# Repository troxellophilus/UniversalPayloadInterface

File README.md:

# UniversalPayloadInterface
Universal UAV Payload Interface Senior Project

Open Source Code & Hardware

Cal Poly SLO

* Nolan Reker
* Drew Troxell
* David Troy

More documentation coming soon!

### Getting Started

#### Requirements
* UAV utilizing the Mavlink protocol
* Onboard proxy device for running MAVProxy
* Atmega328p on payload interface board (see pcb directory for hardware details)

#### Loading the source
* Compile and upload the payload_atmega328p ino project to the atmega328p payload interface board using your favorite AVR compiler/loader.
* Connect the interface board to the onboard device via UART.
* Run MAVProxy on the onboard device w/ the master device set to the autopilot and the output device set to the UART connection to the interface board.
* The onboard LED will light up after successfully receiving 10 heartbeat packets from the autopilot.

#### Modifying the source
This code is meant to provide a simple example and framework for communicating between a payload and an autopilot via Mavlink. Reference the mavlink library for functions to decode or send more messages via mavlink.

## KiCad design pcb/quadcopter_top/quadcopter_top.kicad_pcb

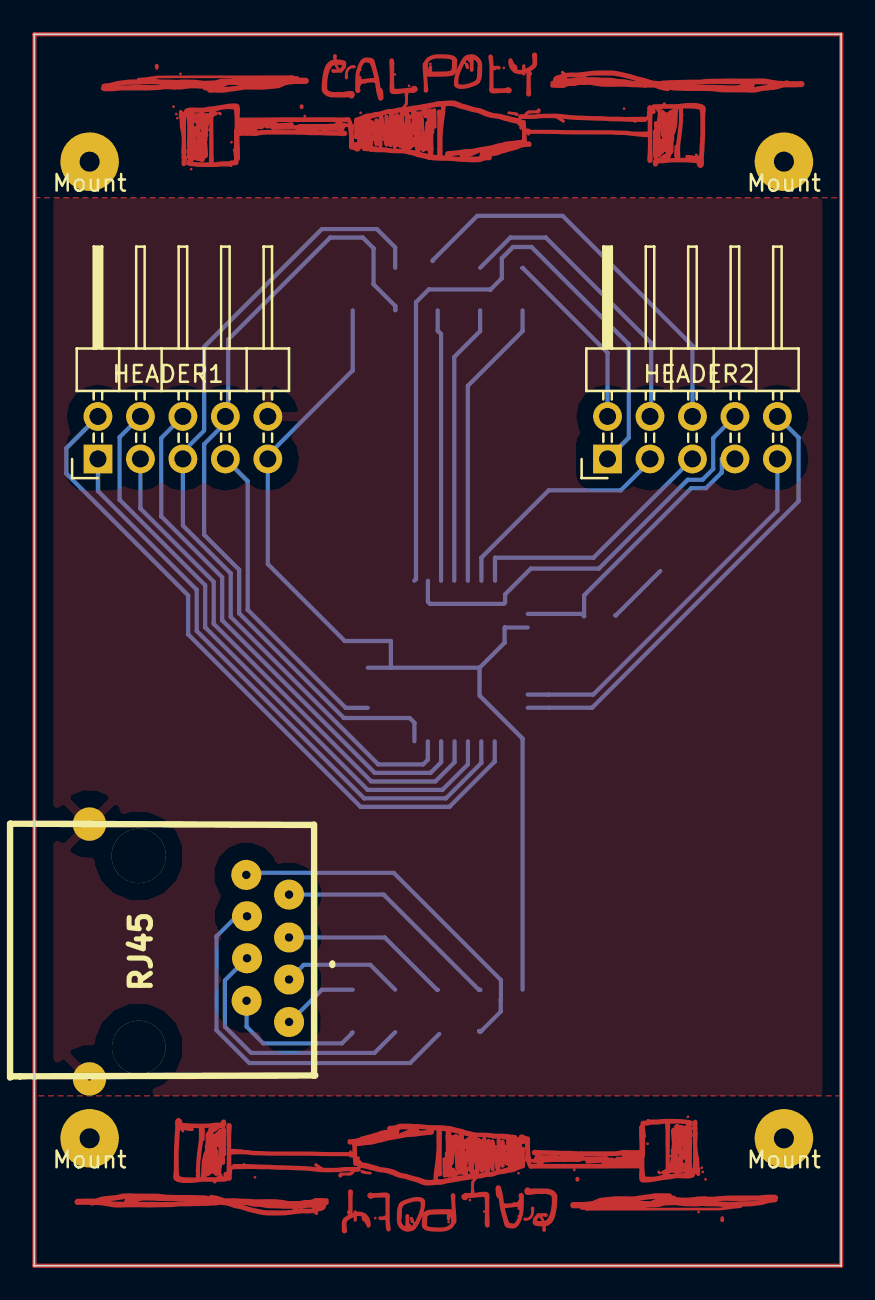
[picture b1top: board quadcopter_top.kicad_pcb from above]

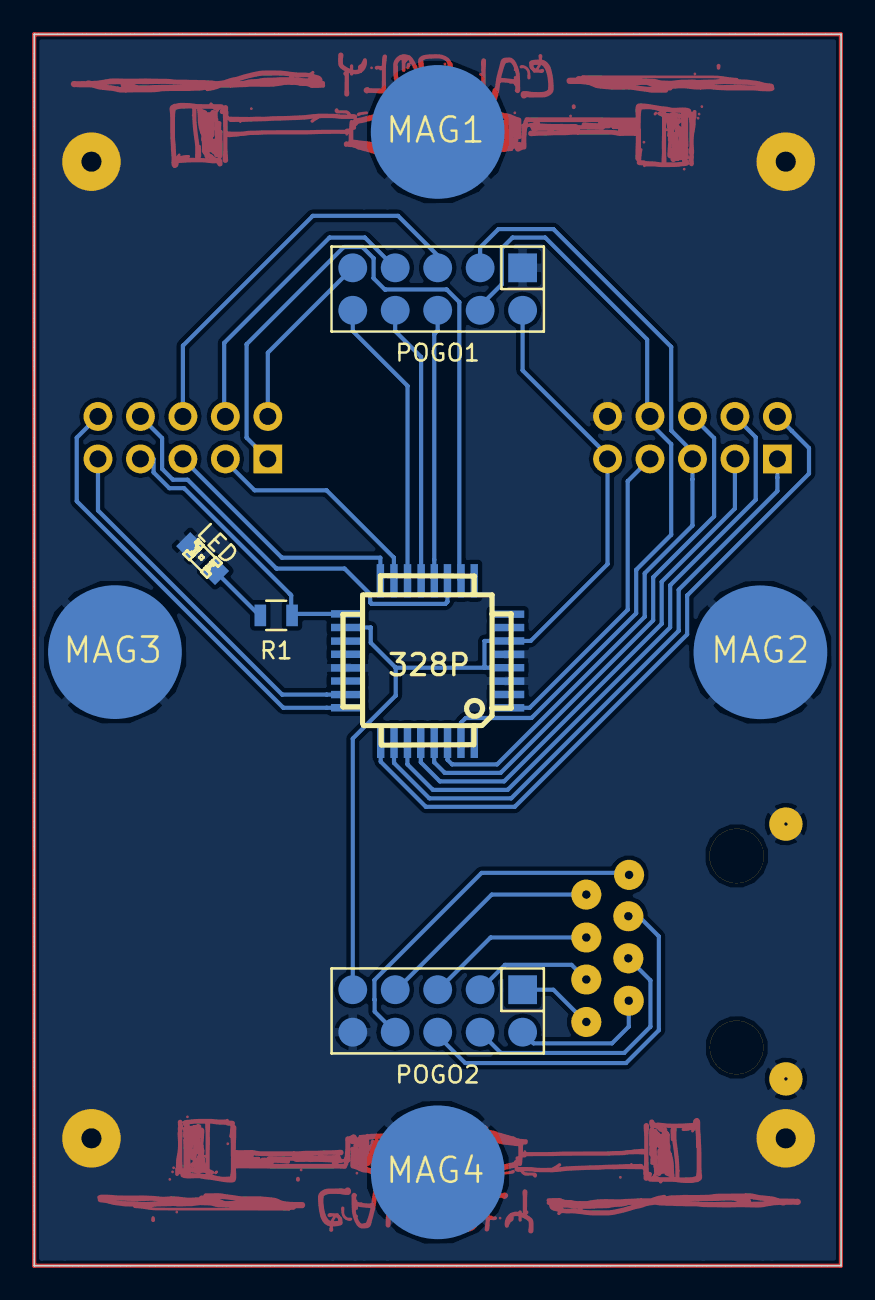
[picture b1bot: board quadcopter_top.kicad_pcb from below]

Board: 2 copper layers, 48.3 x 73.7 mm, 16 parts (9 on the bottom side), 32 nets.

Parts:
328P: ATMEGA328P-A; TQFP32_08
HEADER1, HEADER2: CONN_02X05; Pin_Header_Angled_2x05
J1: RJ45
LED: LED; LED-0805
MAG1, MAG2, MAG3, MAG4: CONN_01X01; 8mmMagnet
Mount: Mount; SolderWirePad_single_1-2mmDrill
Mount#2, Mount#3, Mount#4: Mount; SolderWirePad_single_1-2mmDrill
POGO1, POGO2: CONN_02X05; Pin_Header_Straight_2x05_SMD
R1: R; R_0805

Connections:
+5V: 328P.4, 328P.6, 328P.18, HEADER1.9, POGO1.2, POGO2.9
GND: 328P.3, 328P.5, 328P.21, HEADER1.10, J1.9, LED.1, MAG1.1, MAG2.1, MAG3.1, MAG4.1, POGO1.1, POGO2.10
unnamed: LED.2, R1.2
unnamed: 328P.26, HEADER1.1
unnamed: 328P.25, HEADER1.2
unnamed: 328P.28, HEADER1.3
unnamed: 328P.27, HEADER1.4
unnamed: 328P.30, HEADER1.5, POGO1.3
unnamed: 328P.29, HEADER1.6
unnamed: 328P.1, HEADER1.7
unnamed: 328P.31, HEADER1.8, POGO1.4
unnamed: 328P.10, HEADER2.1
unnamed: HEADER2.2, POGO1.9
unnamed: 328P.15, HEADER2.3
unnamed: HEADER2.4, POGO1.7
unnamed: 328P.16, HEADER2.5
unnamed: HEADER2.6, POGO1.5
unnamed: 328P.17, HEADER2.7, R1.1
unnamed: 328P.11, HEADER2.8
unnamed: 328P.23, HEADER2.9
unnamed: 328P.24, HEADER2.10
unnamed: 328P.12, POGO1.6
unnamed: 328P.13, POGO1.8
unnamed: 328P.14, POGO1.10
unnamed: J1.1, POGO2.8
unnamed: J1.2, POGO2.7
unnamed: J1.3, POGO2.6
unnamed: J1.4, POGO2.5
unnamed: J1.5, POGO2.4
unnamed: J1.6, POGO2.3
unnamed: J1.7, POGO2.2
unnamed: J1.8, POGO2.1

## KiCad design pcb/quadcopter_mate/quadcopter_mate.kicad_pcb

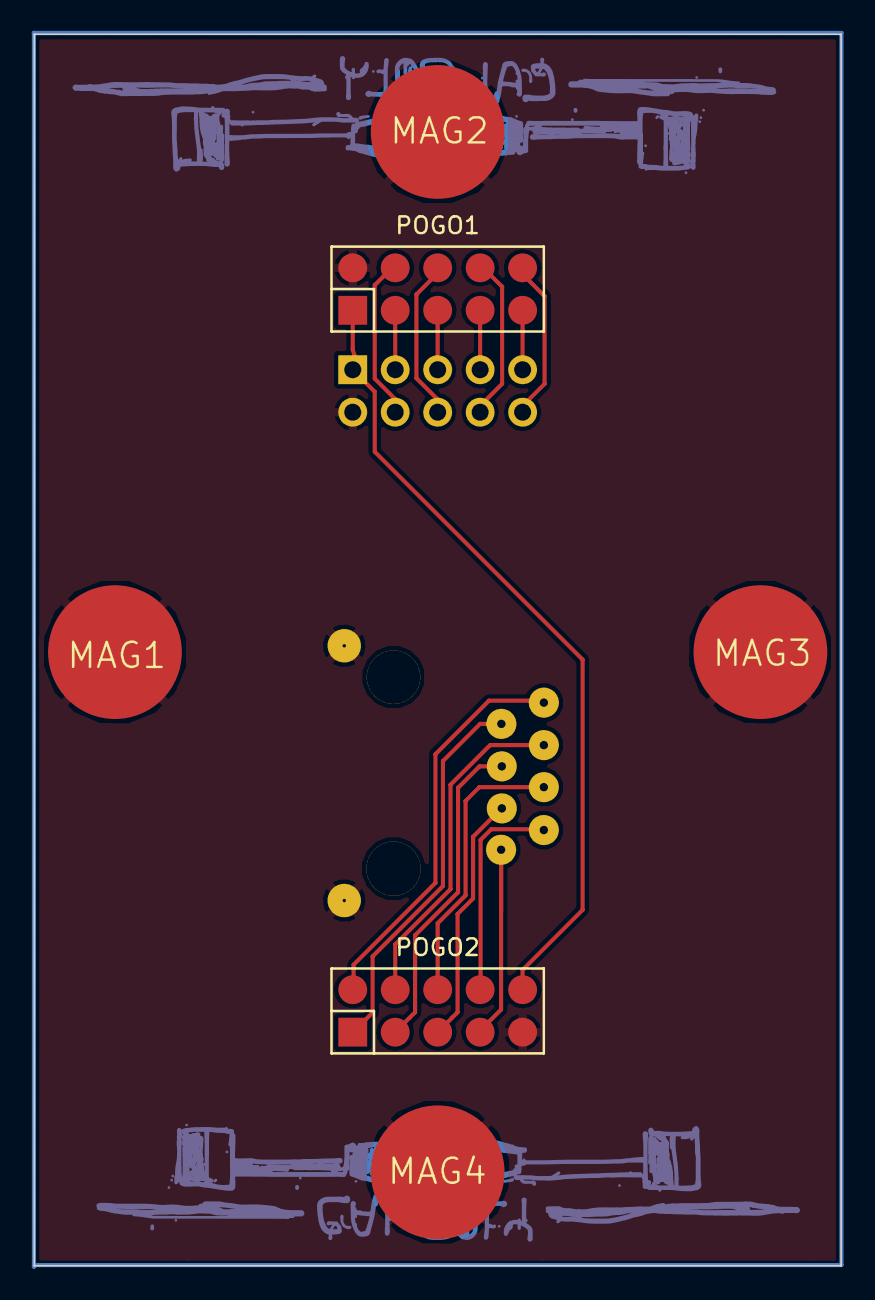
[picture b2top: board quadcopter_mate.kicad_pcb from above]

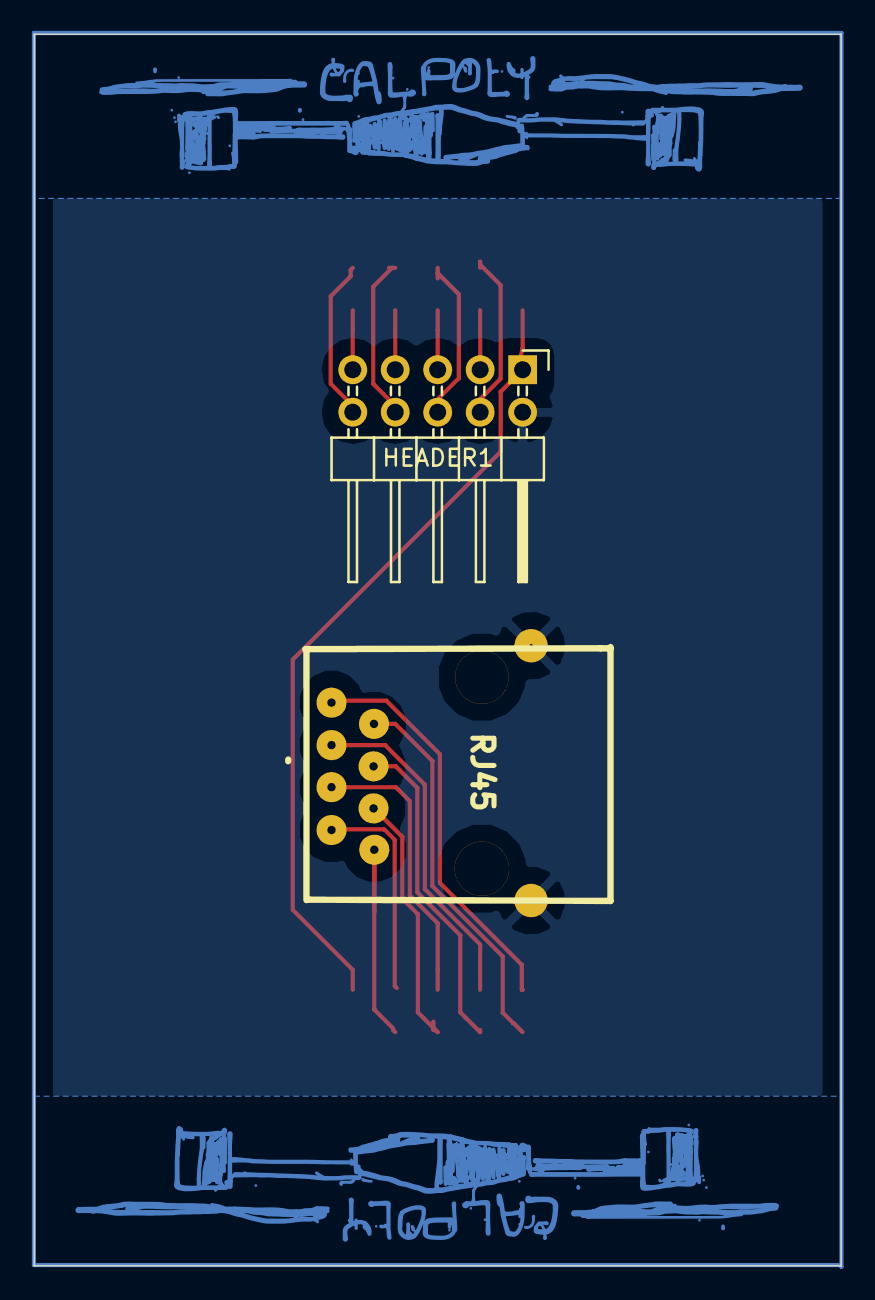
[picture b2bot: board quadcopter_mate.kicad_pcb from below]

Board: 2 copper layers, 48.3 x 73.7 mm, 8 parts (2 on the bottom side), 18 nets.

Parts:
HEADER1: CONN_02X05; Pin_Header_Angled_2x05
J1: RJ45
MAG1, MAG2, MAG3, MAG4: CONN_01X01; 8mmMagnet
POGO1, POGO2: CONN_02X05; Pin_Header_Straight_2x05_SMD

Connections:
+5V: HEADER1.1, POGO1.1, POGO2.10
GND: HEADER1.2, J1.9, MAG1.1, MAG2.1, MAG3.1, MAG4.1, POGO1.2, POGO2.9
unnamed: HEADER1.3, POGO1.3
unnamed: HEADER1.4, POGO1.4
unnamed: HEADER1.5, POGO1.5
unnamed: HEADER1.6, POGO1.6
unnamed: HEADER1.7, POGO1.7
unnamed: HEADER1.8, POGO1.8
unnamed: HEADER1.9, POGO1.9
unnamed: HEADER1.10, POGO1.10
unnamed: J1.1, POGO2.7
unnamed: J1.2, POGO2.8
unnamed: J1.3, POGO2.5
unnamed: J1.4, POGO2.6
unnamed: J1.5, POGO2.3
unnamed: J1.6, POGO2.4
unnamed: J1.7, POGO2.1
unnamed: J1.8, POGO2.2

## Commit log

2015-04-21 Initial commit w/ atmega328p code for MAVLink.
2015-05-06 Removed overlord spy malware
2015-05-06 Added basic payload type definition to MAVlink protocol headers and setup heartbeat to use this definition
2015-05-06 Added delay to slow down heartbeat packets
2015-05-06 Tanked .build/*
2015-05-18 Current state, no correct reception from apm yet.
2015-05-18 omg it sorta works
2015-05-18 omg it sorta works 2
2015-05-18 Consistently gets initial heartbeat after a reset
2015-05-19 added PCB designs
    KiCad PCB designs. The one labeled top is actually bottom. May fix that at some point. Please make sure all references in KiCad files remain relative to the project dir to avoid broken dependencies.
2015-05-19 HEARTBEATS CONSISTENTLY READ, TRIGGER TX RESPONSE
2015-05-19 Added some comments
2015-05-19 Added cal poly logo and set up backside
2015-05-19 changed default outputs directory to share folder between both PCB's
2015-05-27 Mirrored text in mate board to be correct when gerber is mirrored
2015-05-29 (unfinished) tracking variables
2015-05-29 Code structure, comments, successfully sending mission set points.
2015-05-29 fixed silkscreen, added mounting holes, added 3D models
2015-05-29 Added a bit to readme
2015-05-29 Markdown for what?
2015-05-29 Markdown for what??
2015-06-12 Reformatted schematics
2015-06-14 Expo
2015-06-15 Waypoints progress (unfinished).
2015-06-15 Ready for stop and wait testing.
2015-06-15 Uhm...
2015-06-15 progress on wp upload
2015-06-15 small mods
2015-06-15 removed clear before sending waypoints
2015-06-15 identifiers on wps
2015-06-15 Current state, wps still not loading right (but closer).
2015-06-15 Added IDs for payload system and component. Fixed send state resend conditions.
2015-06-15 Fixed timeout on wp send
2015-06-16 Confirmed sending count, receiving req, sending wp. not sure if apm receives wp.
2015-06-16 Added sys and component id set upon connection for waypoint message structs.
2015-06-16 locks up
2015-06-16 WP work
2015-06-16 waypoint protocol successful.
2015-06-16 Flight test code.
2017-11-04 Added license.
